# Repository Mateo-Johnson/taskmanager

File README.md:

# ESP32-S3 E-Ink Task Manager

A low-power task board built with an ESP32 and an e-ink display. It pulls to-do items from a local or cloud source, renders them in a clean, always-readable layout, and updates only when needed to maximize battery life. Meant to be used as a keychain, so must be extremely small!

**3D Model:**

**Layout:**

**Schematic:**

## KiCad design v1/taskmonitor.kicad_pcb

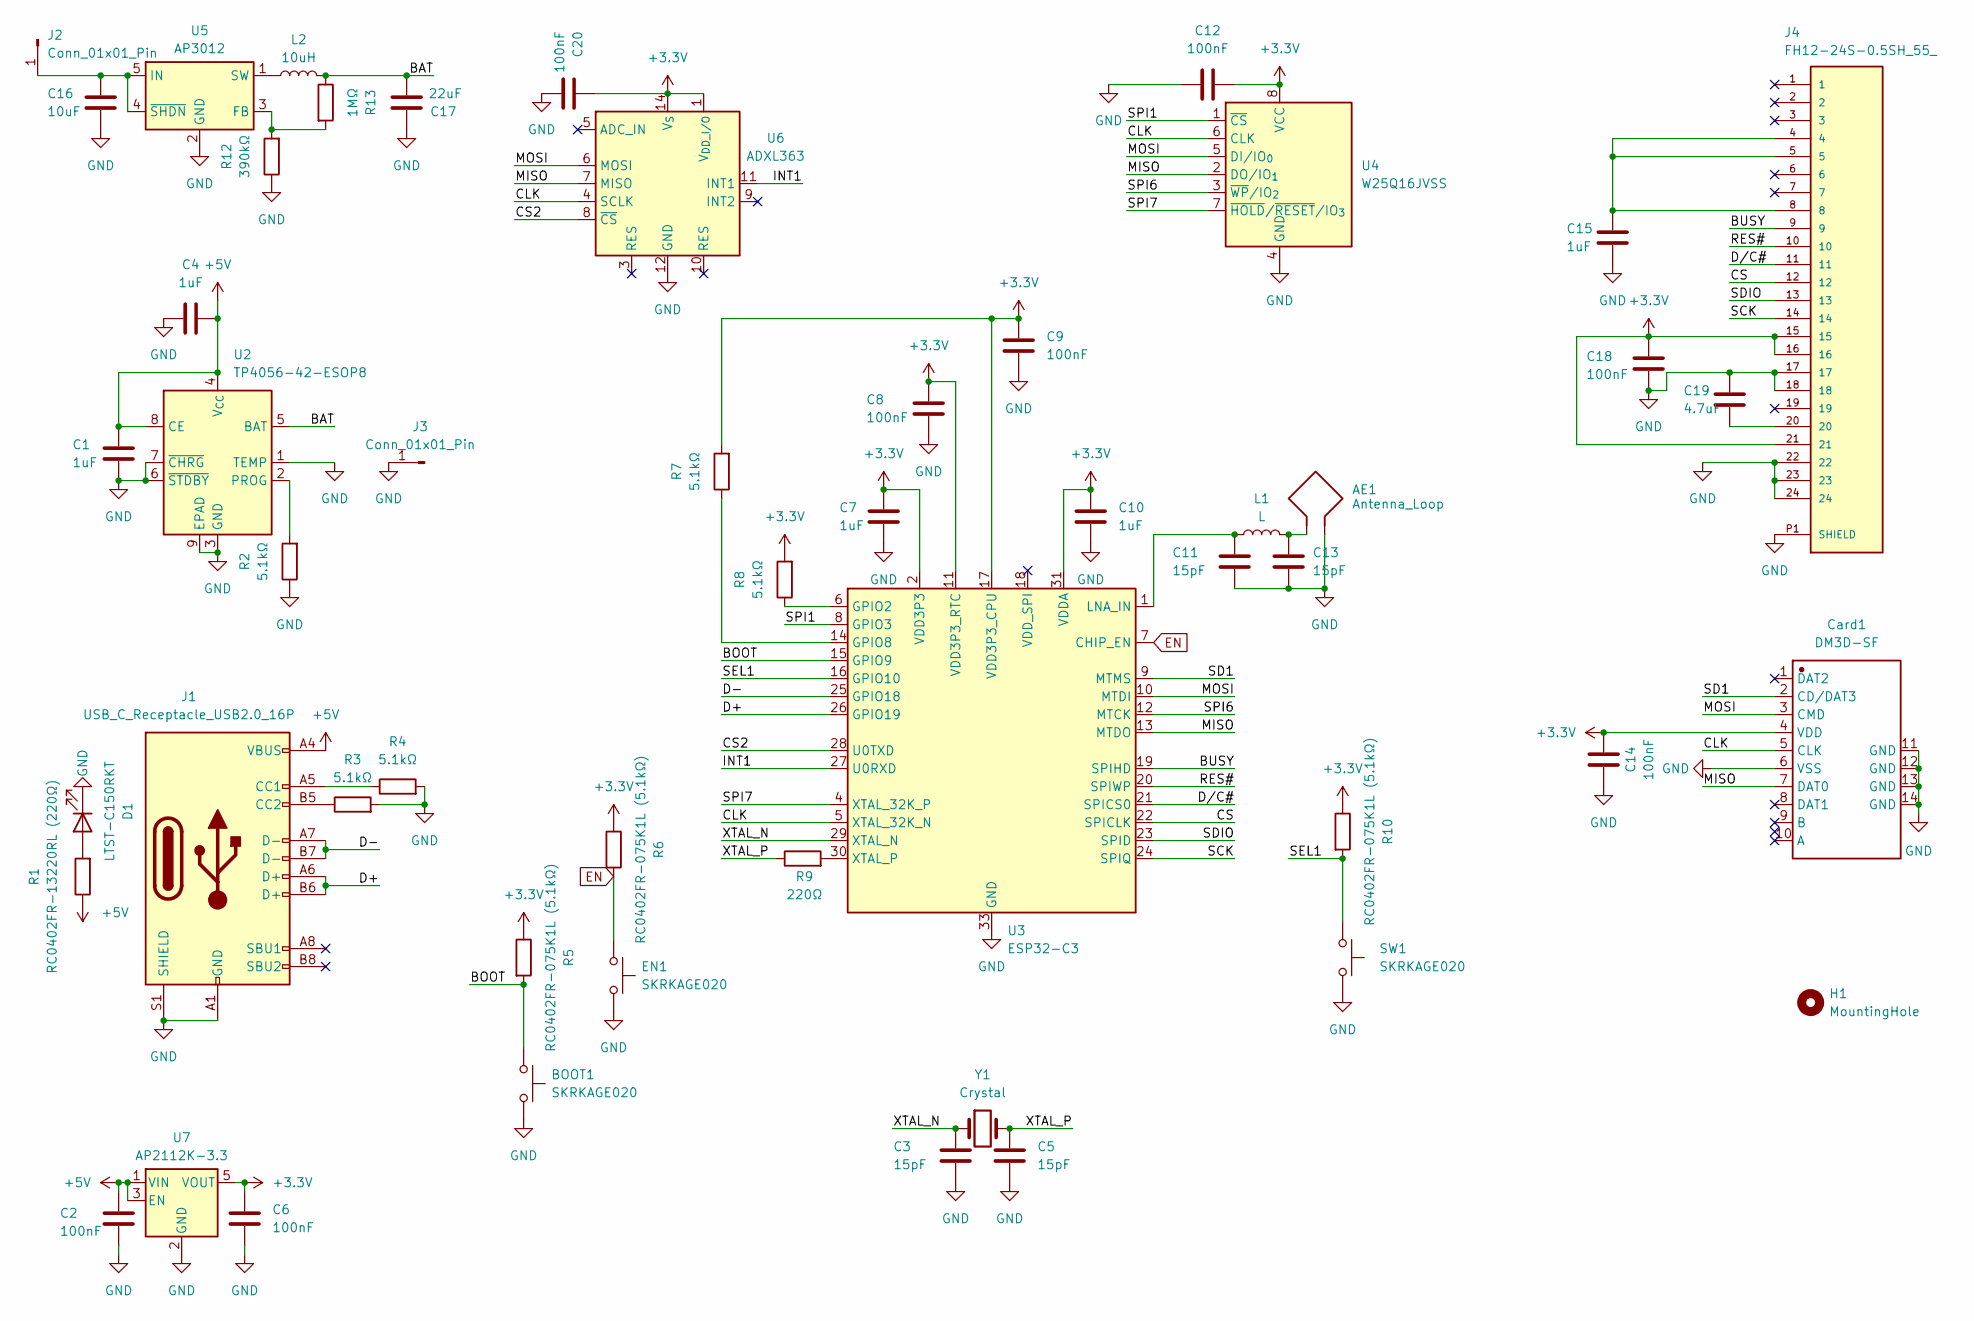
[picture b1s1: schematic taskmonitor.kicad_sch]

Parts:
AE1: Antenna_Loop; Texas_SWRA117D_2.4GHz_Right
BOOT1: SKRKAGE020; SW_Push_SPST_NO_Alps_SKRK
C1, C4, C7, C10, C15: 1uF; C0402
C2, C6, C8, C9, C12, C14, C18, C20: 100nF; C0402
C3, C5, C11, C13: 15pF; C0402
C16: 10uF; C0402
C17: 22uF; C0402
C19: 4.7uF; C0402
Card1: DM3D-SF; TF-SMD_DM3D-SF; Manufacturer Part DM3D-SF
D1: LTST-C150RKT; LED_1206_3216Metric
EN1: SKRKAGE020; SW_Push_SPST_NO_Alps_SKRK
H1: MountingHole; MountingHole_4mm
J1: USB_C_Receptacle_USB2.0_16P; USB_C_Receptacle_HCTL_HC-TYPE-C-16P-01A
J2, J3: Conn_01x01_Pin; TestPoint_Pad_2.5x2.5mm
J4: FH12-24S-0.5SH_55_; Hirose FH12
L1: L; L_01005_0402Metric
L2: 10uH; L_01005_0402Metric
R1: RC0402FR-13220RL (220Ω); R0402
R2, R3, R4, R7, R8: 5.1kΩ; R0402
R5, R6, R10: RC0402FR-075K1L (5.1kΩ); R0402
R9: 220Ω; R0402
R12: 390kΩ; R0402
R13: 1MΩ; R0402
SW1: SKRKAGE020; SW_Push_SPST_NO_Alps_SKRK
U2: TP4056-42-ESOP8; SOIC-8-1EP_3.9x4.9mm_P1.27mm_EP2.41x3.3mm_ThermalVias
U3: ESP32-C3; QFN-32-1EP_5x5mm_P0.5mm_EP3.7x3.7mm
U4: W25Q16JVSS; SOIC-8_5.3x5.3mm_P1.27mm
U5: AP3012; SOT-23-5
U6: ADXL363; Analog_LGA-16_3.25x3mm_P0.5mm_LayoutBorder3x5y
U7: AP2112K-3.3; SOT-23-5
Y1: Crystal; Crystal_SMD_3215-2Pin_3.2x1.5mm

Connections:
+3.3V: C6.1, C7.1, C8.2, C9.1, C10.1, C12.2, C14.1, C18.2, C20.2, Card1.4 (VDD), J4.15, J4.16, J4.21, R5.1, R6.1, R7.2, R8.2, R10.1, U3.2 (VDD3P3), U3.3 (VDD3P3), U3.11 (VDD3P3_RTC), U3.17 (VDD3P3_CPU), U3.31 (VDDA), U3.32 (VDDA), U4.8 (VCC), U6.1 (V_{DD_I/O}), U6.14 (V_{S}), U7.5 (VOUT)
+5V: C1.1, C2.1, C4.2, J1.A4 (VBUS), J1.A9 (VBUS), J1.B4 (VBUS), J1.B9 (VBUS), R1.1, U2.4 (V_{CC}), U2.8 (CE), U7.1 (VIN), U7.3 (EN)
/BAT: C17.2, L2.2, R13.1, U2.5 (BAT)
/BOOT: BOOT1.1, R5.2, U3.15 (GPIO9)
/BUSY: J4.9, U3.19 (SPIHD)
/CLK: Card1.5 (CLK), U3.5 (XTAL_32K_N), U4.6 (CLK), U6.4 (SCLK)
/CS: J4.12, U3.22 (SPICLK)
/CS2: U3.28 (U0TXD), U6.8 (~CS)
/D+: J1.A6 (D+), J1.B6 (D+), U3.26 (GPIO19)
/D-: J1.A7 (D-), J1.B7 (D-), U3.25 (GPIO18)
/D/C#: J4.11, U3.21 (SPICS0)
/INT1: U3.27 (U0RXD), U6.11 (INT1)
/MISO: Card1.7 (DAT0), U3.13 (MTDO), U4.2 (DO/IO_{1}), U6.7 (MISO)
/MOSI: Card1.3 (CMD), U3.10 (MTDI), U4.5 (DI/IO_{0}), U6.6 (MOSI)
/RES#: J4.10, U3.20 (SPIWP)
/SCK: J4.14, U3.24 (SPIQ)
/SD1: Card1.2 (CD/DAT3), U3.9 (MTMS)
/SDIO: J4.13, U3.23 (SPID)
/SEL1: R10.2, SW1.1, U3.16 (GPIO10)
/SPI1: U3.8 (GPIO3), U4.1 (~CS)
/SPI6: U3.12 (MTCK), U4.3 (~WP/IO_{2})
/SPI7: U3.4 (XTAL_32K_P), U4.7 (~HOLD/~RESET/IO_{3})
/XTAL_N: C3.2, U3.29 (XTAL_N), Y1.1
/XTAL_P: C5.1, R9.1, Y1.2
EN: EN1.1, R6.2, U3.7 (CHIP_EN)
GND: AE1.2, BOOT1.2, C1.2, C2.2, C3.1, C4.1, C5.2, C6.2, C7.2, C8.1, C9.2, C10.2, C11.1, C12.1, C13.1, C14.2, C15.1, C16.1, C17.1, C18.1, C19.2, C20.1, Card1.6 (VSS), Card1.11 (GND), Card1.12 (GND), Card1.13 (GND), Card1.14 (GND), D1.1 (K), EN1.2, J1.A1 (GND), J1.A12 (GND), J1.B1 (GND), J1.B12 (GND), J1.S1 (SHIELD), J3.1, J4.17, J4.18, J4.22, J4.23, J4.24, J4.P1 (SHIELD), J4.P2 (SHIELD), R2.1, R3.2, R4.2, R12.1, SW1.2, U2.1 (TEMP), U2.3 (GND), U2.6 (~STDBY), U2.7 (~CHRG), U2.9 (EPAD), U3.33 (GND), U4.4 (GND), U5.2 (GND), U6.12 (GND), U6.13 (GND), U6.16 (GND), U7.2 (GND)
unnamed: AE1.1, C13.2, L1.2
unnamed: C15.2, J4.4, J4.5, J4.8
unnamed: C19.1, J4.20
unnamed: D1.2 (A), R1.2
unnamed: J1.A5 (CC1), R4.1
unnamed: J1.B5 (CC2), R3.1
unnamed: C16.2, J2.1, U5.4 (~SHDN), U5.5 (IN)
unnamed: R2.2, U2.2 (PROG)
unnamed: R8.1, U3.6 (GPIO2)
unnamed: R7.1, U3.14 (GPIO8)
unnamed: C11.2, L1.1, U3.1 (LNA_IN)
unnamed: R9.2, U3.30 (XTAL_P)
unnamed: R12.2, R13.2, U5.3 (FB)
unnamed: L2.1, U5.1 (SW)

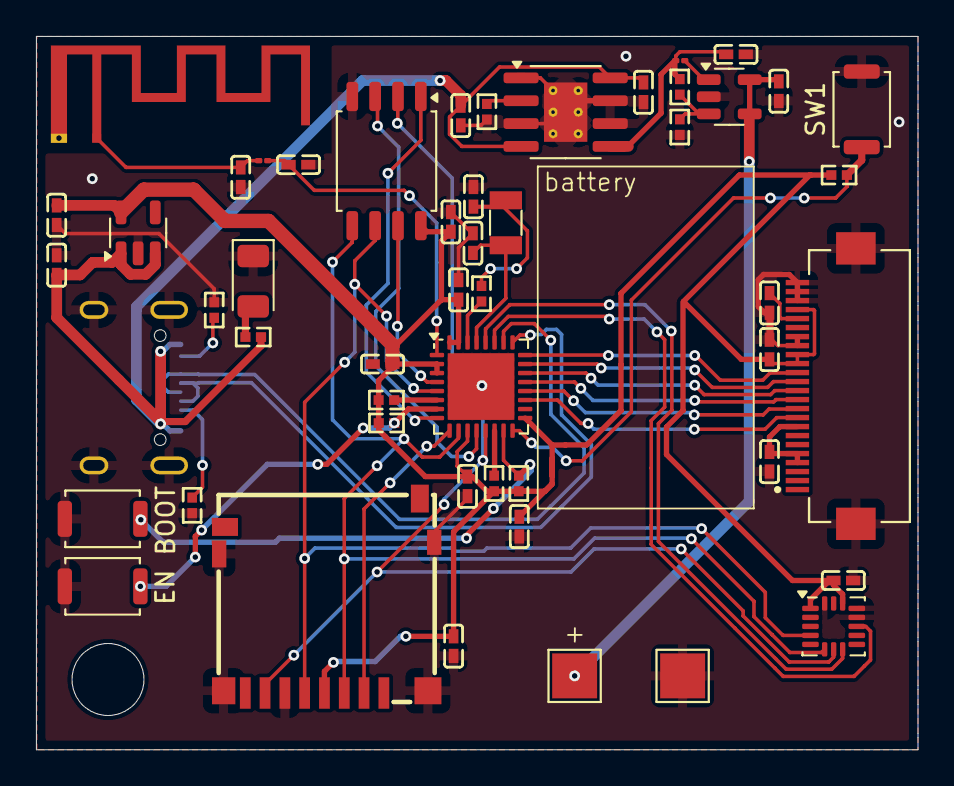
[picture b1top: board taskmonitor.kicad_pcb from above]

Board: 2 copper layers, 49.0 x 39.6 mm, 52 parts (1 on the bottom side), 40 nets.

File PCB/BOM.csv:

"Reference","Qty","Value","DNP","Exclude from BOM","Exclude from Board","Footprint","Datasheet"
"AE1","1","Antenna_Loop","","","","RF_Antenna:Texas_SWRA117D_2.4GHz_Right","~"
"BOOT1,EN1,SW1","3","SKRKAGE020","","","","Button_Switch_SMD:SW_Push_SPST_NO_Alps_SKRK","~"
"C1,C4,C7,C10,C15","5","1uF","","","","10uF:C0402","~"
"C2,C6,C8,C9,C12,C14,C18,C20","8","100nF","","","","10uF:C0402","~"
"C3,C5,C11,C13","4","15pF","","","","10uF:C0402","~"
"C16","1","10uF","","","","10uF:C0402","~"
"C17","1","22uF","","","","10uF:C0402","~"
"C19","1","4.7uF","","","","10uF:C0402","~"
"Card1","1","DM3D-SF","","","","DM3D:TF-SMD_DM3D-SF",""
"D1","1","LTST-C150RKT","","","","LED_SMD:LED_1206_3216Metric","~"
"H1","1","MountingHole","","Excluded from BOM","","MountingHole:MountingHole_4mm","~"
"J1","1","USB_C_Receptacle_USB2.0_16P","","","","Connector_USB:USB_C_Receptacle_HCTL_HC-TYPE-C-16P-01A","https://www.usb.org/sites/default/files/documents/usb_type-c.zip"
"J2,J3","2","Conn_01x01_Pin","","","","TestPoint:TestPoint_Pad_2.5x2.5mm","~"
"J4","1","FH12-24S-0.5SH_55_","","","","Hirose FH12:Hirose FH12",""
"L1","1","L","","","","Inductor_SMD:L_01005_0402Metric","~"
"L2","1","10uH","","","","Inductor_SMD:L_01005_0402Metric","~"
"R1","1","RC0402FR-13220RL (220Ω)","","","","0402:R0402","~"
"R2,R3,R4,R7,R8","5","5.1kΩ","","","","0402:R0402","~"
"R5,R6,R10","3","RC0402FR-075K1L (5.1kΩ)","","","","0402:R0402","~"
"R9","1","220Ω","","","","0402:R0402","~"
"R12","1","390kΩ","","","","0402:R0402","~"
"R13","1","1MΩ","","","","0402:R0402","~"
"U2","1","TP4056-42-ESOP8","","","","Package_SO:SOIC-8-1EP_3.9x4.9mm_P1.27mm_EP2.41x3.3mm_ThermalVias","https://www.lcsc.com/datasheet/lcsc_datasheet_2410121619_TOP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"
"U3","1","ESP32-C3","","","","Package_DFN_QFN:QFN-32-1EP_5x5mm_P0.5mm_EP3.7x3.7mm","https://www.espressif.com/sites/default/files/documentation/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"
"U4","1","W25Q16JVSS","","","","Package_SO:SOIC-8_5.3x5.3mm_P1.27mm","https://www.winbond.com/hq/support/documentation/levelOne.js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"
"U5","1","AP3012","","","","Package_TO_SOT_SMD:SOT-23-5","https://www.diodes.com/assets/Datasheets/AP3012.pdf"
"U6","1","ADXL363","","","","Sensor_Motion:Analog_LGA-16_3.25x3mm_P0.5mm_LayoutBorder3x5y","https://www.analog.com/media/en/technical-documentation/data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"
"U7","1","AP2112K-3.3","","","","Package_TO_SOT_SMD:SOT-23-5","https://www.diodes.com/assets/Datasheets/AP2112.pdf"
"Y1","1","Crystal","","","","Crystal:Crystal_SMD_3215-2Pin_3.2x1.5mm","~"

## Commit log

2025-12-06 Enhance README with project details and visuals
    Added project description and images for 3D model, layout, and schematic.
2025-12-06 Update README with images for project details
    Added images for 3D model, layout, and schematic.
2025-12-06 Format README sections with bold titles
2025-12-07 Rename taskmonitor.csv to BOM.csv
